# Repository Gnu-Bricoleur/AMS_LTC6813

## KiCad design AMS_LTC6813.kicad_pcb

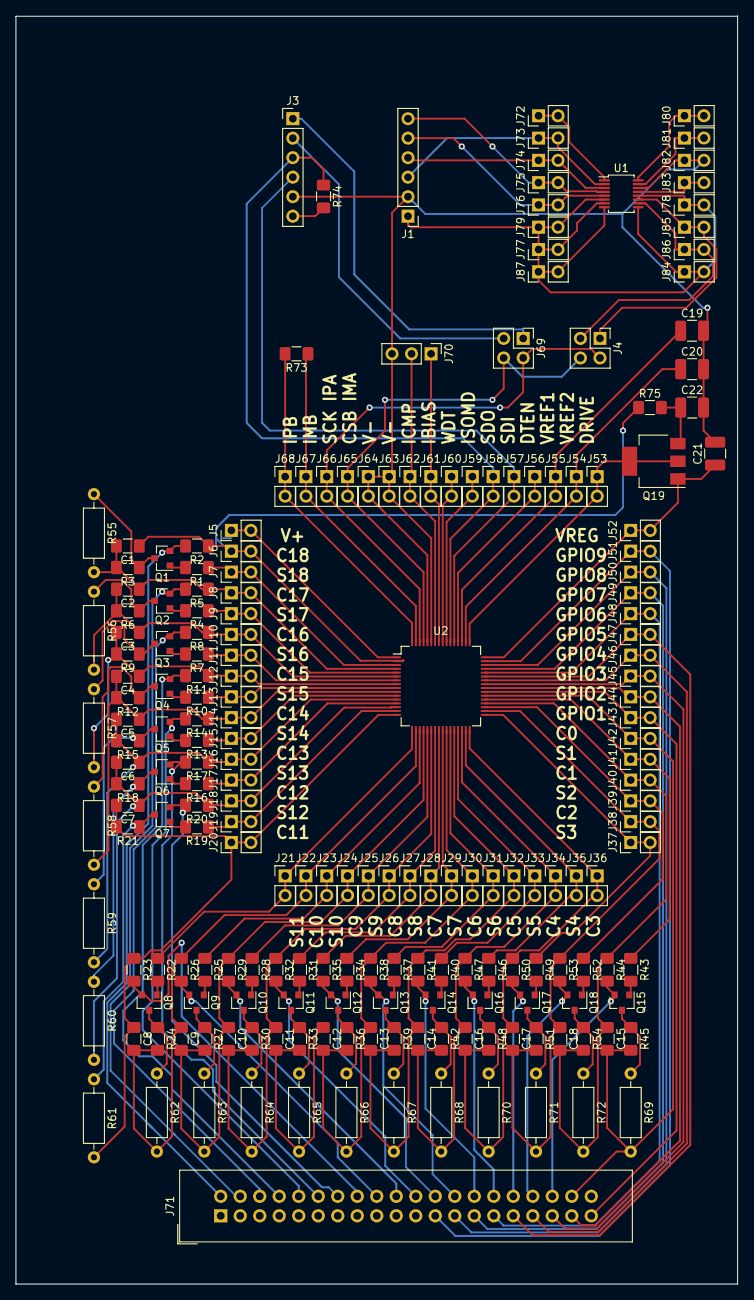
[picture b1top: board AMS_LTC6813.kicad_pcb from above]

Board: 2 copper layers, 94.0 x 165.2 mm, 204 parts (0 on the bottom side), 131 nets.

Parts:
C1, C2, C3, C4, C5, C6, C7, C8, C9, C10, C11, C12, C13, C14, C15, C16, C17, C18: 10n; R_1206_3216Metric_Pad1.42x1.75mm_HandSolder
C19, C20, C21: 1u; C_1210_3225Metric_Pad1.42x2.65mm_HandSolder
C22: 0.1u; C_1210_3225Metric_Pad1.42x2.65mm_HandSolder
J1, J3: Conn_01x06; PinHeader_1x06_P2.54mm_Vertical
J4, J69: Conn_02x02_Counter_Clockwise; PinHeader_2x02_P2.54mm_Vertical
J5, J6, J7, J8, J9, J10, J11, J12, J13, J14, J15, J16, J17, J18, J19, J20, J21, J22, J23, J24, J25, J26, J27, J28, J29, J30, J31, J32, J33, J34, J35, J36, J37, J38, J39, J40, J41, J42, J43, J44, J45, J46, J47, J48, J49, J50, J51, J52, J53, J54, J55, J56, J57, J58, J59, J60, J61, J62, J63, J64, J65, J66, J67, J68, J72, J73, J74, J75, J76, J77, J78, J79, J80, J81, J82, J83, J84, J85, J86, J87: Conn_01x02_Male; PinHeader_1x02_P2.54mm_Vertical
J70: Conn_01x03_Female; PinHeader_1x03_P2.54mm_Vertical
J71: Conn_02x20_Counter_Clockwise; IDC-Header_2x20_P2.54mm_Vertical
Q1, Q2, Q3, Q4, Q5, Q6, Q7, Q8, Q9, Q10, Q11, Q12, Q13, Q14, Q15, Q16, Q17, Q18: BSS138; SOT-23
Q19: 2N2219; SOT-223-3_TabPin2
R1, R4, R7, R10, R13, R16, R19, R22, R25, R28, R31, R34, R37, R40, R43, R46, R49, R52: 3.3k; R_1206_3216Metric_Pad1.42x1.75mm_HandSolder
R2, R5, R8, R11, R14, R17, R20, R23, R26, R29, R32, R35, R38, R41, R44, R47, R50, R53, R73: 100; R_1206_3216Metric_Pad1.42x1.75mm_HandSolder
R3, R6, R9, R12, R15, R18, R21, R24, R27, R30, R33, R36, R39, R42, R45, R48, R51, R54: 33; R_1206_3216Metric_Pad1.42x1.75mm_HandSolder
R55, R56, R57, R58, R59, R60, R61, R62, R63, R64, R65, R66, R67, R68, R69, R70, R71, R72: 33; R_Axial_DIN0207_L6.3mm_D2.5mm_P10.16mm_Horizontal
R74: 5k; R_1206_3216Metric_Pad1.42x1.75mm_HandSolder
R75: R; R_1206_3216Metric_Pad1.42x1.75mm_HandSolder
U1: LTC6820; MSOP-16_3x4mm_P0.5mm
U2: LTC6813-1; LQFP-64_10x10mm_P0.5mm

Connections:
/C: C22.1, Q19.3, R75.2
/C0: C15.2, C19.2, C20.2, C21.2, C22.2, J1.2, J3.5, J42.1, J42.2, J63.1, J63.2, J64.1, J64.2, J70.3, J71.38, J82.1, J82.2, R45.2, R69.2, U1.14, U2.38, U2.59, U2.60
/C1: C15.1, C18.2, J40.1, J40.2, R44.1, R54.2, R72.2, U2.36
/C2: C17.2, C18.1, J38.1, J38.2, R51.2, R53.1, R71.2, U2.34
/C3: C16.2, C17.1, J36.1, J36.2, R48.2, R50.1, R70.2, U2.32
/C4: C14.2, C16.1, J34.1, J34.2, R42.2, R47.1, R68.2, U2.30
/C5: C13.2, C14.1, J32.1, J32.2, R39.2, R41.1, R67.2, U2.28
/C6: C12.2, C13.1, J30.1, J30.2, R36.2, R38.1, R66.2, U2.26
/C7: C11.2, C12.1, J28.1, J28.2, R33.2, R35.1, R65.2, U2.24
/C8: C10.2, C11.1, J26.1, J26.2, R30.2, R32.1, R64.2, U2.22
/C9: C9.2, C10.1, J24.1, J24.2, R27.2, R29.1, R63.2, U2.20
/C10: C8.2, C9.1, J22.1, J22.2, R24.2, R26.1, R62.2, U2.18
/C11: C7.2, C8.1, J20.1, J20.2, R21.2, R23.1, R61.2, U2.16
/C12: C6.2, C7.1, J18.1, J18.2, R18.2, R20.1, R60.2, U2.14
/C13: C5.2, C6.1, J16.1, J16.2, R15.2, R17.1, R59.2, U2.12
/C14: C4.2, C5.1, J14.1, J14.2, R12.2, R14.1, R58.2, U2.10
/C15: C3.2, C4.1, J12.1, J12.2, R9.2, R11.1, R57.2, U2.8
/C16: C2.2, C3.1, J10.1, J10.2, R6.2, R8.1, R56.2, U2.6
/C17: C1.2, C2.1, J8.1, J8.2, R3.2, R5.1, R55.2, U2.4
/C18: C1.1, J6.1, J6.2, R2.1, R75.1, U2.2
/CELL1: J71.36, Q15.2, R44.2
/CELL2: J71.34, Q18.2, R53.2
/CELL3: J71.32, Q17.2, R50.2
/CELL4: J71.30, Q16.2, R47.2
/CELL5: J71.28, Q14.2, R41.2
/CELL6: J71.26, Q13.2, R38.2
/CELL7: J71.24, Q12.2, R35.2
/CELL8: J71.22, Q11.2, R32.2
/CELL9: J71.20, Q10.2, R29.2
/CELL10: J71.18, Q9.2, R26.2
/CELL11: J71.16, Q8.2, R23.2
/CELL12: J71.14, Q7.2, R20.2
/CELL13: J71.12, Q6.2, R17.2
/CELL14: J71.10, Q5.2, R14.2
/CELL15: J71.8, Q4.2, R11.2
/CELL16: J71.6, Q3.2, R8.2
/CELL17: J71.4, Q2.2, R5.2
/CELL18: J71.2, Q1.2, R2.2
/CS: J1.5, J76.1, J76.2, U1.5
/CSBIMA: J4.4, J65.1, J65.2, J69.4, U2.61
/CSBIMA1: J3.2, J69.3
/DRIVE: J53.1, J53.2, Q19.2, U2.49
/DTEN: J56.1, J56.2, U2.52
/EN: J72.1, J72.2, U1.1
/GPIO1: J43.1, J43.2, J71.39, U2.39
/GPIO2: J44.1, J44.2, J71.37, U2.40
/GPIO3: J45.1, J45.2, J71.35, U2.41
/GPIO4: J46.1, J46.2, J71.33, U2.42
/GPIO5: J47.1, J47.2, J71.31, U2.43
/GPIO6: J48.1, J48.2, J71.29, U2.44
/GPIO7: J49.1, J49.2, J71.27, U2.45
/GPIO8: J50.1, J50.2, J71.25, U2.46
/GPIO9: J51.1, J51.2, J71.23, U2.47
/IBIAS: J61.1, J61.2, J70.1, U2.57
/IBIAS1: J80.1, J80.2, U1.16
/ICMP: J62.1, J62.2, J70.2, U2.58
/ICMP1: J81.1, J81.2, U1.15
/IM: J4.3, J86.1, J86.2, U1.10
/IMB: J67.1, J67.2, R73.1, U2.63
/IP: J4.1, J85.1, J85.2, U1.11
/IPB: J68.1, J68.2, R73.2, U2.64
/ISOMD: J59.1, J59.2, U2.55
/MISO: J1.4, J74.1, J74.2, U1.3
/MOSI: J1.3, J73.1, J73.2, U1.2
/S1: J41.1, J41.2, R43.1, U2.37
/S2: J39.1, J39.2, R52.1, U2.35
/S3: J37.1, J37.2, R49.1, U2.33
/S4: J35.1, J35.2, R46.1, U2.31
/S5: J33.1, J33.2, R40.1, U2.29
/S6: J31.1, J31.2, R37.1, U2.27
/S7: J29.1, J29.2, R34.1, U2.25
/S8: J27.1, J27.2, R31.1, U2.23
/S9: J25.1, J25.2, R28.1, U2.21
/S10: J23.1, J23.2, R25.1, U2.19
/S11: J21.1, J21.2, R22.1, U2.17
/S12: J19.1, J19.2, R19.1, U2.15
/S13: J17.1, J17.2, R16.1, U2.13
/S14: J15.1, J15.2, R13.1, U2.11
/S15: J13.1, J13.2, R10.1, U2.9
/S16: J11.1, J11.2, R7.1, U2.7
/S17: J9.1, J9.2, R4.1, U2.5
/S18: J7.1, J7.2, R1.1, U2.3
/SCK: J1.6, J75.1, J75.2, U1.4
/SCKIPA: J4.2, J66.1, J66.2, J69.2, U2.62
/SCKIPA1: J3.1, J69.1
/SDI: J3.4, J57.1, J57.2, U2.53
/SDO: J3.3, J58.1, J58.2, R74.1, U2.54
/SLOW: J83.1, J83.2, U1.13
/V+: J5.1, J5.2, U2.1
/VDD1: J1.1, J77.1, J77.2, J78.1, J78.2, J79.1, J79.2, J84.1, J84.2, J87.1, J87.2, U1.6, U1.7, U1.8, U1.9, U1.12
/VDD2: J3.6, R74.2
/VREF1: C19.1, J55.1, J55.2, U2.51
/VREF2: C20.1, J54.1, J54.2, U2.50
/VREG: C21.1, J52.1, J52.2, Q19.1, U2.48
/WDT: J60.1, J60.2, U2.56
unnamed: Q1.1, R1.2
unnamed: Q1.3, R3.1, R55.1
unnamed: Q2.1, R4.2
unnamed: Q2.3, R6.1, R56.1
unnamed: Q3.1, R7.2
unnamed: Q3.3, R9.1, R57.1
unnamed: Q4.1, R10.2
unnamed: Q4.3, R12.1, R58.1
unnamed: Q5.1, R13.2
unnamed: Q5.3, R15.1, R59.1
unnamed: Q6.1, R16.2
unnamed: Q6.3, R18.1, R60.1
unnamed: Q7.1, R19.2
unnamed: Q7.3, R21.1, R61.1
unnamed: Q8.1, R22.2
unnamed: Q8.3, R24.1, R62.1
unnamed: Q9.1, R25.2
unnamed: Q9.3, R27.1, R63.1
unnamed: Q10.1, R28.2
unnamed: Q10.3, R30.1, R64.1
unnamed: Q11.1, R31.2
unnamed: Q11.3, R33.1, R65.1
unnamed: Q12.1, R34.2
unnamed: Q12.3, R36.1, R66.1
unnamed: Q13.1, R37.2
unnamed: Q13.3, R39.1, R67.1
unnamed: Q14.1, R40.2
unnamed: Q14.3, R42.1, R68.1
unnamed: Q15.1, R43.2
unnamed: Q15.3, R45.1, R69.1
unnamed: Q16.1, R46.2
unnamed: Q16.3, R48.1, R70.1
unnamed: Q17.1, R49.2
unnamed: Q17.3, R51.1, R71.1
unnamed: Q18.1, R52.2
unnamed: Q18.3, R54.1, R72.1

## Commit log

2020-04-28 putting online
2020-05-10 4 archive 10/05/20
2020-10-23 working on a newer version
2020-10-25 adding com
2020-10-25 blabl
2020-10-28 petite modif
2020-11-08 tout route sauf voltage channel
2020-11-08 voltages partiellements route
2020-11-09 routing everything
